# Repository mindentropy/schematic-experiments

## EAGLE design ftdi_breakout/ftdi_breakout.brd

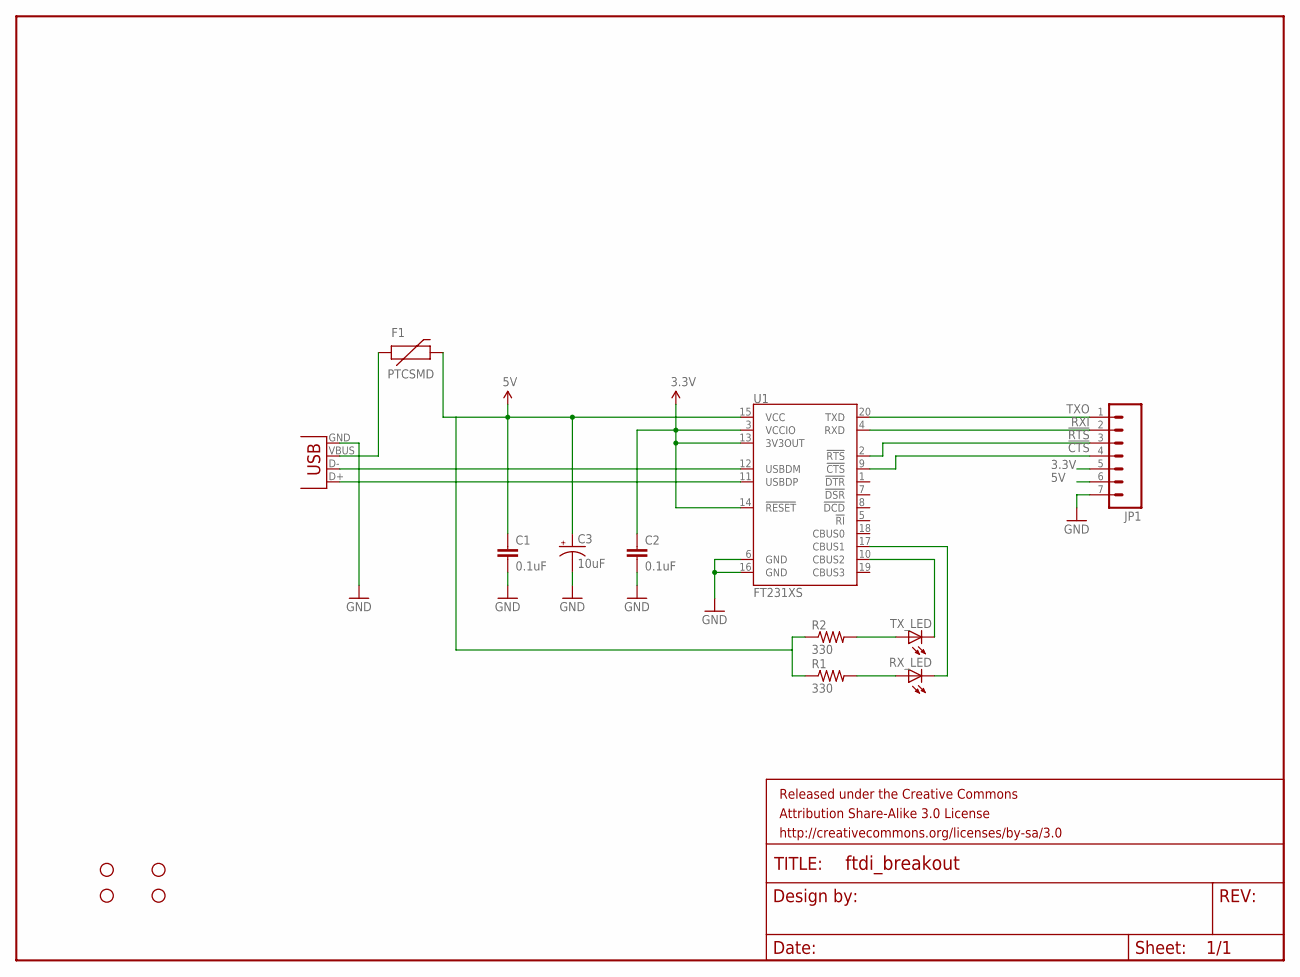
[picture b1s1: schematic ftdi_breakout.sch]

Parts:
C1, C2: 0.1uF; 0603-CAP
C3: 10uF; EIA3216
F1: PTCSMD; PTC-1206
FRAME1: FRAME-LETTER; CREATIVE_COMMONS
JP1: M07; 1X07
JP3: USBSMD; USB-MINIB
R1, R2: 330; 0603-RES
RX_LED: LED0603; LED-0603
STANDOFF1, STANDOFF2, STANDOFF3, STANDOFF4: STAND-OFF
TX_LED: LED0603; LED-0603
U1: FT231XS; SSOP20_L

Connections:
3.3V: C2.1, JP1.5, U1.3 (VCCIO), U1.13 (3V3OUT), U1.14 (!RESET)
5V: C1.1, C3.A (+), F1.2, JP1.6, R1.1, R2.1, U1.15 (VCC)
!CTS: JP1.4, U1.9 (!CTS)
!RTS: JP1.3, U1.2 (!RTS)
GND: C1.2, C2.2, C3.C (-), JP1.7, JP3.GND, U1.6 (GND), U1.16 (GND)
unnamed: JP3.D+, U1.11 (USBDP)
unnamed: F1.1, JP3.VBUS
unnamed: JP3.D-, U1.12 (USBDM)
unnamed: RX_LED.C, U1.17 (CBUS1)
unnamed: TX_LED.C, U1.10 (CBUS2)
unnamed: R2.2, TX_LED.A
unnamed: R1.2, RX_LED.A
RXI: JP1.2, U1.4 (RXD)
TXO: JP1.1, U1.20 (TXD)

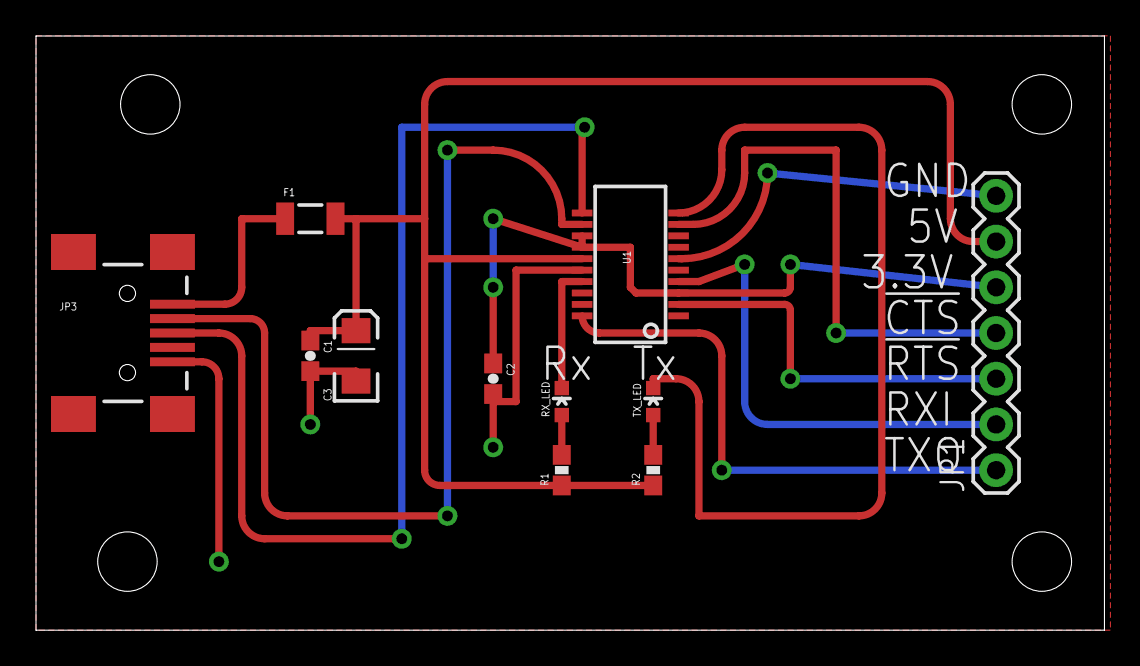
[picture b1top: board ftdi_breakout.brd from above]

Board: 2 copper layers, 59.4 x 33.0 mm, 16 parts (0 on the bottom side), 14 nets.

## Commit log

2013-08-05 Initial ftdi breakout board commit.
2013-08-06 Modified to connect the chip as sinking the current from LED.
2013-08-07 Modified layout file.
2015-03-14 Migrating wiki contents from Google Code

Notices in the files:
parts and their libraries:
SparkFun-Aesthetics: Licensing: CC v3.0 Share-Alike You are welcome to use this library for commercial purposes.
SparkFun-Aesthetics: Released under the Creative Commons Attribution Share-Alike 3.0 License
SparkFun-Aesthetics: http://creativecommons.org/licenses/by-sa/3.0
